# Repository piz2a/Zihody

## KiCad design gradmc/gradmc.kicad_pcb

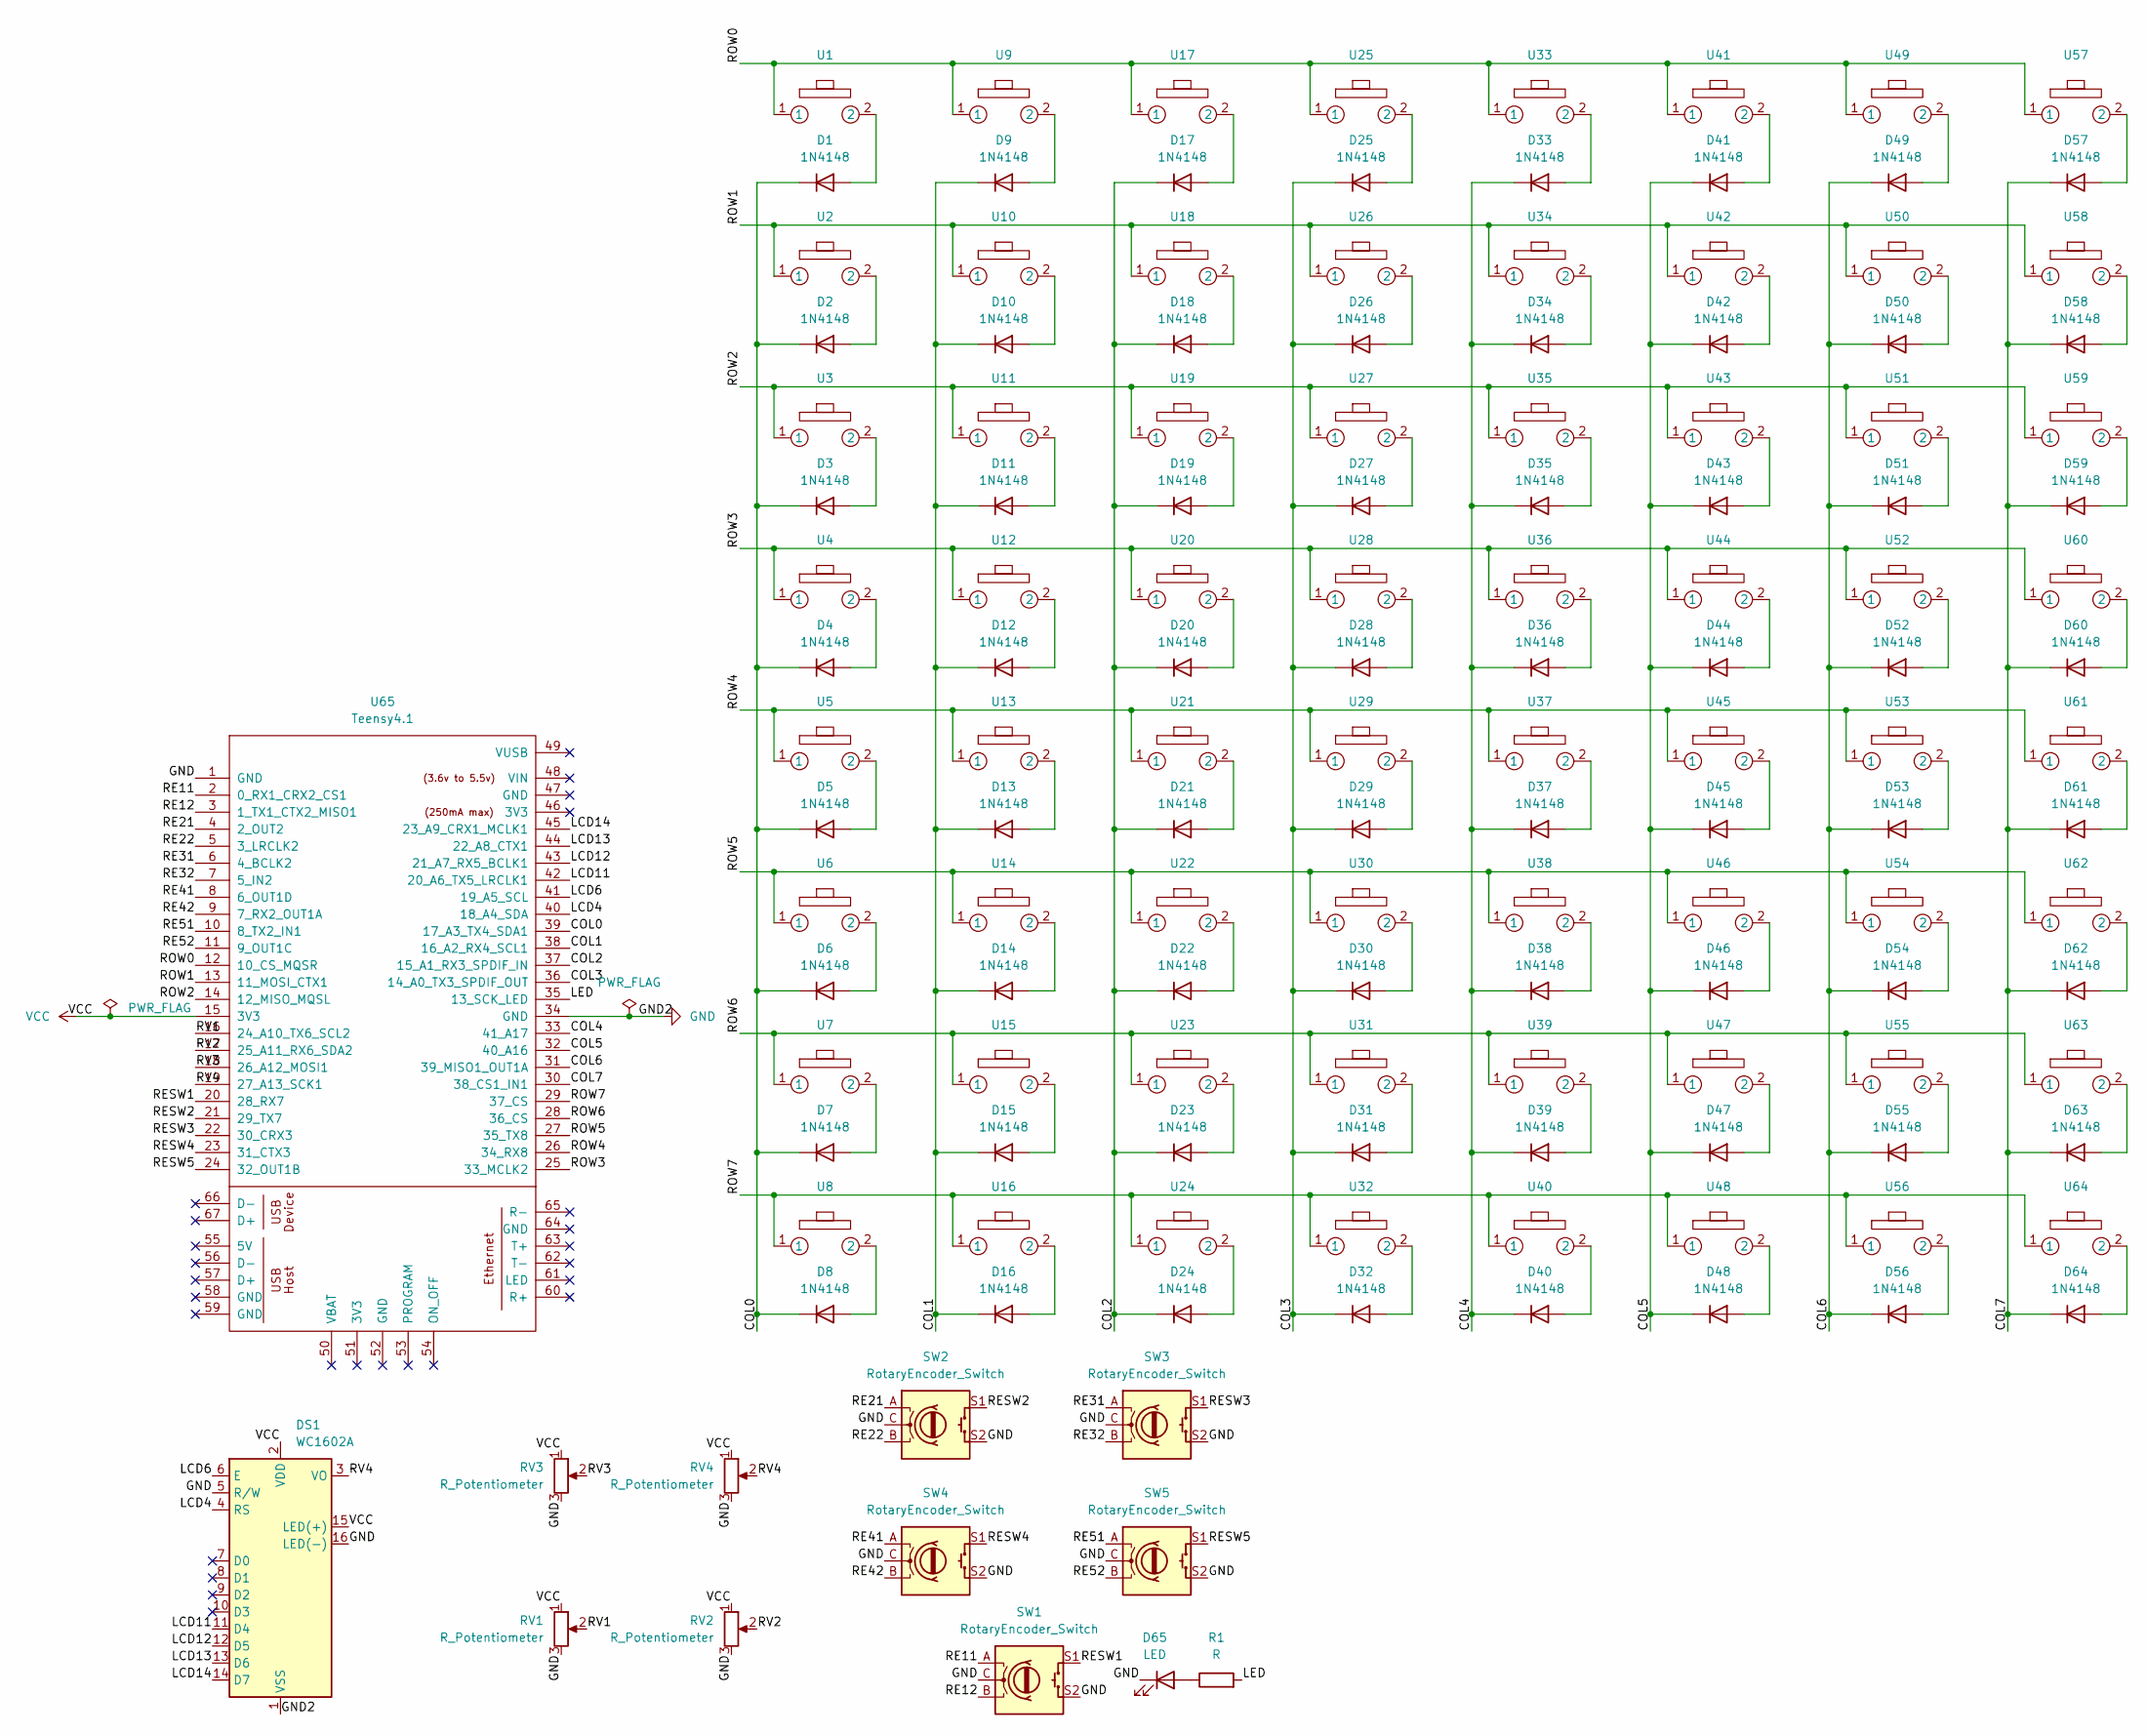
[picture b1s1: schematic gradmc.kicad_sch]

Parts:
D1, D2, D3, D4, D5, D6, D7, D8, D9, D10, D11, D12, D13, D14, D15, D16, D17, D18, D19, D20, D21, D22, D23, D24, D25, D26, D27, D28, D29, D30, D31, D32, D33, D34, D35, D36, D37, D38, D39, D40, D41, D42, D43, D44, D45, D46, D47, D48, D49, D50, D51, D52, D53, D54, D55, D56, D57, D58, D59, D60, D61, D62, D63, D64: 1N4148; D_DO-35_SOD27_P7.62mm_Horizontal
D65: LED; LED_D5.0mm_FlatTop
DS1: WC1602A
R1: R; R_Axial_DIN0309_L9.0mm_D3.2mm_P12.70mm_Horizontal
RV1, RV2: R_Potentiometer; Potentiometer_Bourns_PTA6043_Single_Slide
RV3, RV4: R_Potentiometer; Potentiometer_RV09H_20SQ_Single_Vertical
SW1, SW2, SW3, SW4, SW5: RotaryEncoder_Switch; RotaryEncoder_Alps_EC11E-Switch_Vertical_H20mm
U1, U2, U3, U4, U5, U6, U7, U8, U9, U10, U11, U12, U13, U14, U15, U16, U17, U18, U19, U20, U21, U22, U23, U24, U25, U26, U27, U28, U29, U30, U31, U32, U33, U34, U35, U36, U37, U38, U39, U40, U41, U42, U43, U44, U45, U46, U47, U48, U49, U50, U51, U52, U53, U54, U55, U56, U57, U58, U59, U60, U61, U62, U63, U64: SW_Cherry_MX_1.00u_PCB
U65: Teensy4.1; Teensy41

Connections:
/COL0: D1.1 (K), D2.1 (K), D3.1 (K), D4.1 (K), D5.1 (K), D6.1 (K), D7.1 (K), D8.1 (K), U65.39 (17_A3_TX4_SDA1)
/COL1: D9.1 (K), D10.1 (K), D11.1 (K), D12.1 (K), D13.1 (K), D14.1 (K), D15.1 (K), D16.1 (K), U65.38 (16_A2_RX4_SCL1)
/COL2: D17.1 (K), D18.1 (K), D19.1 (K), D20.1 (K), D21.1 (K), D22.1 (K), D23.1 (K), D24.1 (K), U65.37 (15_A1_RX3_SPDIF_IN)
/COL3: D25.1 (K), D26.1 (K), D27.1 (K), D28.1 (K), D29.1 (K), D30.1 (K), D31.1 (K), D32.1 (K), U65.36 (14_A0_TX3_SPDIF_OUT)
/COL4: D33.1 (K), D34.1 (K), D35.1 (K), D36.1 (K), D37.1 (K), D38.1 (K), D39.1 (K), D40.1 (K), U65.33 (41_A17)
/COL5: D41.1 (K), D42.1 (K), D43.1 (K), D44.1 (K), D45.1 (K), D46.1 (K), D47.1 (K), D48.1 (K), U65.32 (40_A16)
/COL6: D49.1 (K), D50.1 (K), D51.1 (K), D52.1 (K), D53.1 (K), D54.1 (K), D55.1 (K), D56.1 (K), U65.31 (39_MISO1_OUT1A)
/COL7: D57.1 (K), D58.1 (K), D59.1 (K), D60.1 (K), D61.1 (K), D62.1 (K), D63.1 (K), D64.1 (K), U65.30 (38_CS1_IN1)
/LCD4: DS1.4 (RS), U65.40 (18_A4_SDA)
/LCD6: DS1.6 (E), U65.41 (19_A5_SCL)
/LCD11: DS1.11 (D4), U65.42 (20_A6_TX5_LRCLK1)
/LCD12: DS1.12 (D5), U65.43 (21_A7_RX5_BCLK1)
/LCD13: DS1.13 (D6), U65.44 (22_A8_CTX1)
/LCD14: DS1.14 (D7), U65.45 (23_A9_CRX1_MCLK1)
/LED: R1.2, U65.35 (13_SCK_LED)
/RE11: SW1.A, U65.2 (0_RX1_CRX2_CS1)
/RE12: SW1.B, U65.3 (1_TX1_CTX2_MISO1)
/RE21: SW2.A, U65.4 (2_OUT2)
/RE22: SW2.B, U65.5 (3_LRCLK2)
/RE31: SW3.A, U65.6 (4_BCLK2)
/RE32: SW3.B, U65.7 (5_IN2)
/RE41: SW4.A, U65.8 (6_OUT1D)
/RE42: SW4.B, U65.9 (7_RX2_OUT1A)
/RE51: SW5.A, U65.10 (8_TX2_IN1)
/RE52: SW5.B, U65.11 (9_OUT1C)
/RESW1: SW1.S1, U65.20 (28_RX7)
/RESW2: SW2.S1, U65.21 (29_TX7)
/RESW3: SW3.S1, U65.22 (30_CRX3)
/RESW4: SW4.S1, U65.23 (31_CTX3)
/RESW5: SW5.S1, U65.24 (32_OUT1B)
/ROW0: U1.1, U9.1, U17.1, U25.1, U33.1, U41.1, U49.1, U57.1, U65.12 (10_CS_MQSR)
/ROW1: U2.1, U10.1, U18.1, U26.1, U34.1, U42.1, U50.1, U58.1, U65.13 (11_MOSI_CTX1)
/ROW2: U3.1, U11.1, U19.1, U27.1, U35.1, U43.1, U51.1, U59.1, U65.14 (12_MISO_MQSL)
/ROW3: U4.1, U12.1, U20.1, U28.1, U36.1, U44.1, U52.1, U60.1, U65.25 (33_MCLK2)
/ROW4: U5.1, U13.1, U21.1, U29.1, U37.1, U45.1, U53.1, U61.1, U65.26 (34_RX8)
/ROW5: U6.1, U14.1, U22.1, U30.1, U38.1, U46.1, U54.1, U62.1, U65.27 (35_TX8)
/ROW6: U7.1, U15.1, U23.1, U31.1, U39.1, U47.1, U55.1, U63.1, U65.28 (36_CS)
/ROW7: U8.1, U16.1, U24.1, U32.1, U40.1, U48.1, U56.1, U64.1, U65.29 (37_CS)
/RV1: RV1.2, U65.16 (24_A10_TX6_SCL2)
/RV2: RV2.2, U65.17 (25_A11_RX6_SDA2)
/RV3: RV3.2, U65.18 (26_A12_MOSI1)
/RV4: DS1.3 (VO), RV4.2, U65.19 (27_A13_SCK1)
GND: D65.1 (K), DS1.1 (VSS), DS1.5 (R/W), DS1.16 (LED(-)), RV1.3, RV2.3, RV3.3, RV4.3, SW1.C, SW1.S2, SW2.C, SW2.S2, SW3.C, SW3.S2, SW4.C, SW4.S2, SW5.C, SW5.S2, U65.1 (GND), U65.34 (GND)
unnamed: D1.2 (A), U1.2
unnamed: D2.2 (A), U2.2
unnamed: D3.2 (A), U3.2
unnamed: D4.2 (A), U4.2
unnamed: D5.2 (A), U5.2
unnamed: D6.2 (A), U6.2
unnamed: D7.2 (A), U7.2
unnamed: D8.2 (A), U8.2
unnamed: D9.2 (A), U9.2
unnamed: D10.2 (A), U10.2
unnamed: D11.2 (A), U11.2
unnamed: D12.2 (A), U12.2
unnamed: D13.2 (A), U13.2
unnamed: D14.2 (A), U14.2
unnamed: D15.2 (A), U15.2
unnamed: D16.2 (A), U16.2
unnamed: D17.2 (A), U17.2
unnamed: D18.2 (A), U18.2
unnamed: D19.2 (A), U19.2
unnamed: D20.2 (A), U20.2
unnamed: D21.2 (A), U21.2
unnamed: D22.2 (A), U22.2
unnamed: D23.2 (A), U23.2
unnamed: D24.2 (A), U24.2
unnamed: D25.2 (A), U25.2
unnamed: D26.2 (A), U26.2
unnamed: D27.2 (A), U27.2
unnamed: D28.2 (A), U28.2
unnamed: D29.2 (A), U29.2
unnamed: D30.2 (A), U30.2
unnamed: D31.2 (A), U31.2
unnamed: D32.2 (A), U32.2
unnamed: D33.2 (A), U33.2
unnamed: D34.2 (A), U34.2
unnamed: D35.2 (A), U35.2
unnamed: D36.2 (A), U36.2
unnamed: D37.2 (A), U37.2
unnamed: D38.2 (A), U38.2
unnamed: D39.2 (A), U39.2
unnamed: D40.2 (A), U40.2
unnamed: D41.2 (A), U41.2
unnamed: D42.2 (A), U42.2
unnamed: D43.2 (A), U43.2
unnamed: D44.2 (A), U44.2
unnamed: D45.2 (A), U45.2
unnamed: D46.2 (A), U46.2
unnamed: D47.2 (A), U47.2
unnamed: D48.2 (A), U48.2
unnamed: D49.2 (A), U49.2
unnamed: D50.2 (A), U50.2
unnamed: D51.2 (A), U51.2
unnamed: D52.2 (A), U52.2
unnamed: D53.2 (A), U53.2
unnamed: D54.2 (A), U54.2
unnamed: D55.2 (A), U55.2
unnamed: D56.2 (A), U56.2
unnamed: D57.2 (A), U57.2
unnamed: D58.2 (A), U58.2
unnamed: D59.2 (A), U59.2
unnamed: D60.2 (A), U60.2
unnamed: D61.2 (A), U61.2
unnamed: D62.2 (A), U62.2
unnamed: D63.2 (A), U63.2
unnamed: D64.2 (A), U64.2
unnamed: D65.2 (A), R1.1
VCC: DS1.2 (VDD), DS1.15 (LED(+)), RV1.1, RV2.1, RV3.1, RV4.1, U65.15 (3V3)

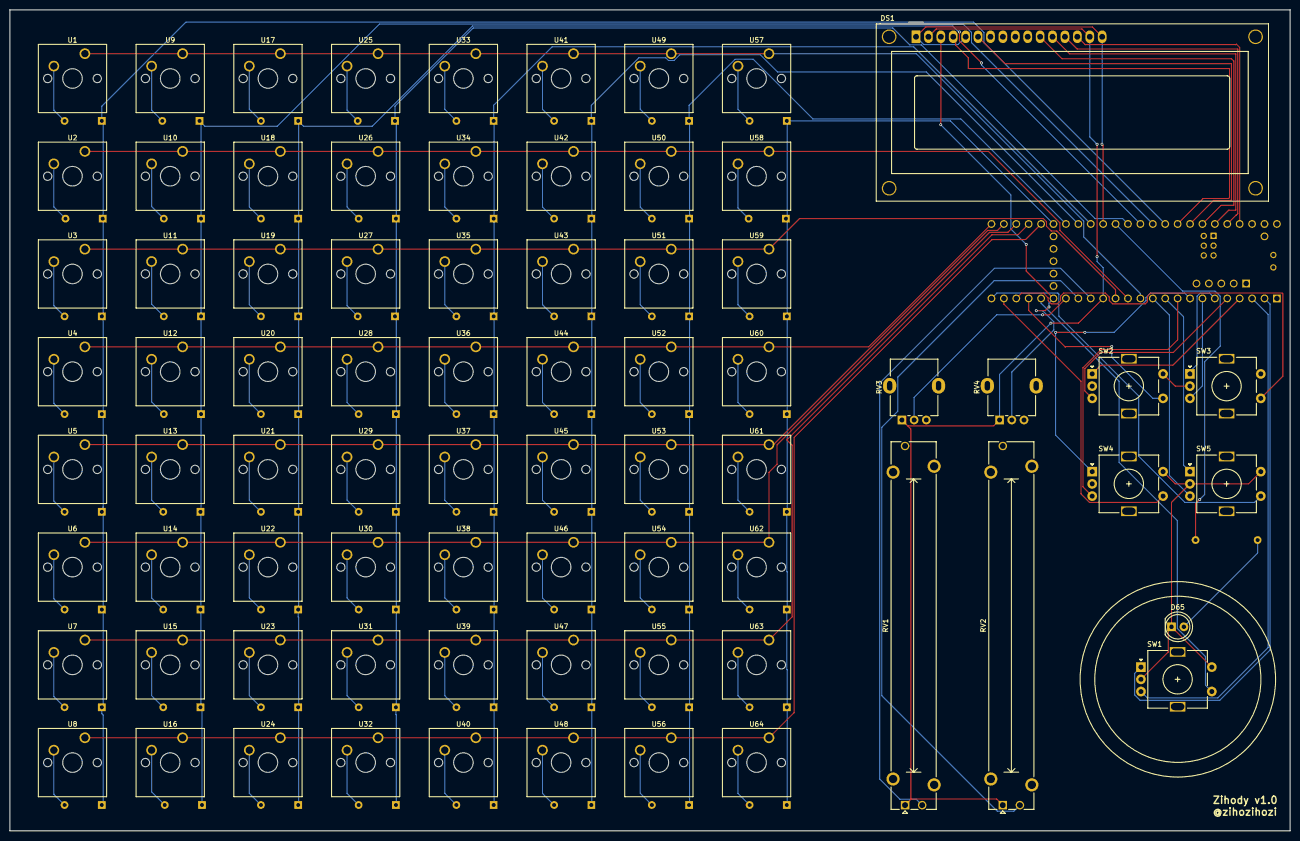
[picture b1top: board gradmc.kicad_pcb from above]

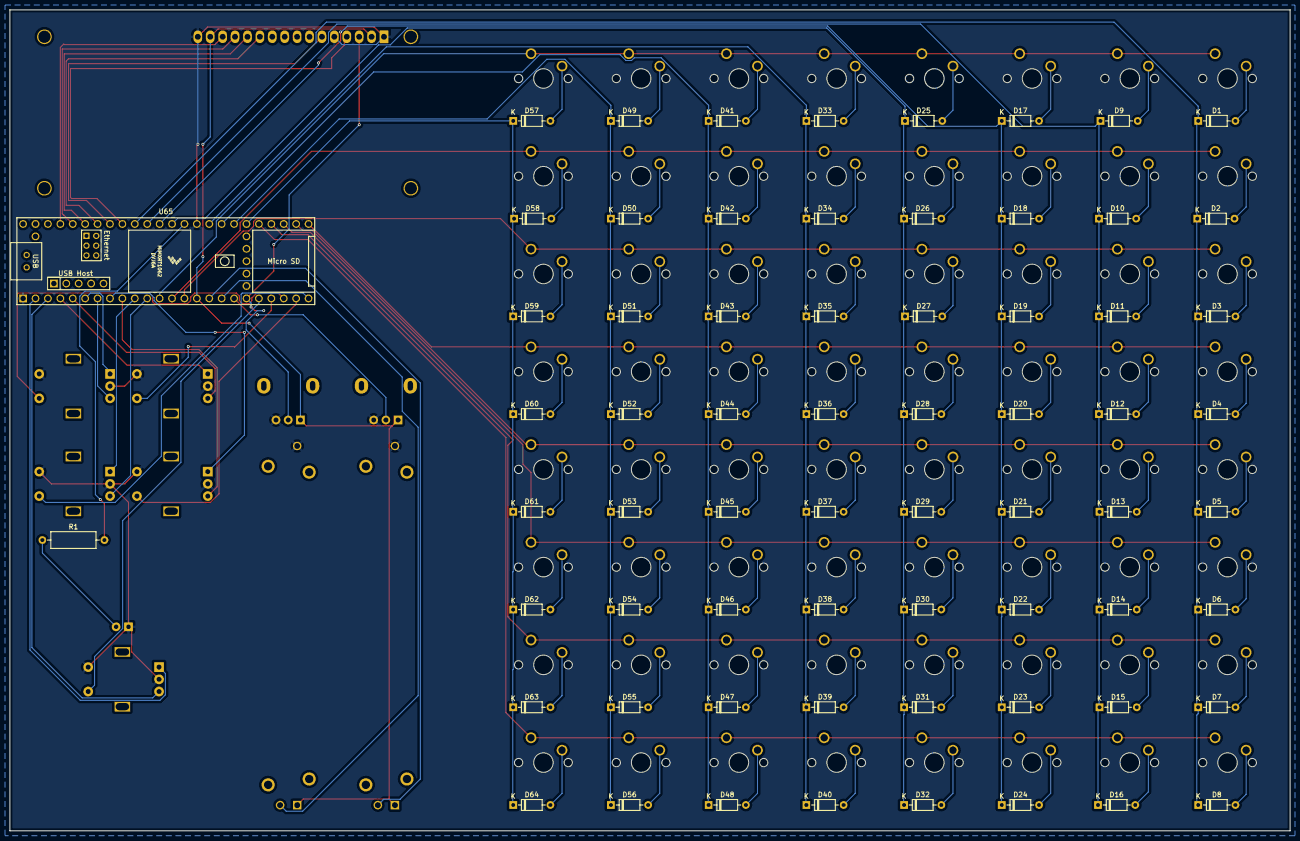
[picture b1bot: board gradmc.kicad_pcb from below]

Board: 2 copper layers, 262.0 x 168.0 mm, 141 parts (66 on the bottom side), 109 nets.

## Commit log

2024-12-16 Add files
